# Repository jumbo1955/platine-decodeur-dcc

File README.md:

platine-decodeur-dcc

Schématiques et PCB pour décodeur DCC de locomotives N

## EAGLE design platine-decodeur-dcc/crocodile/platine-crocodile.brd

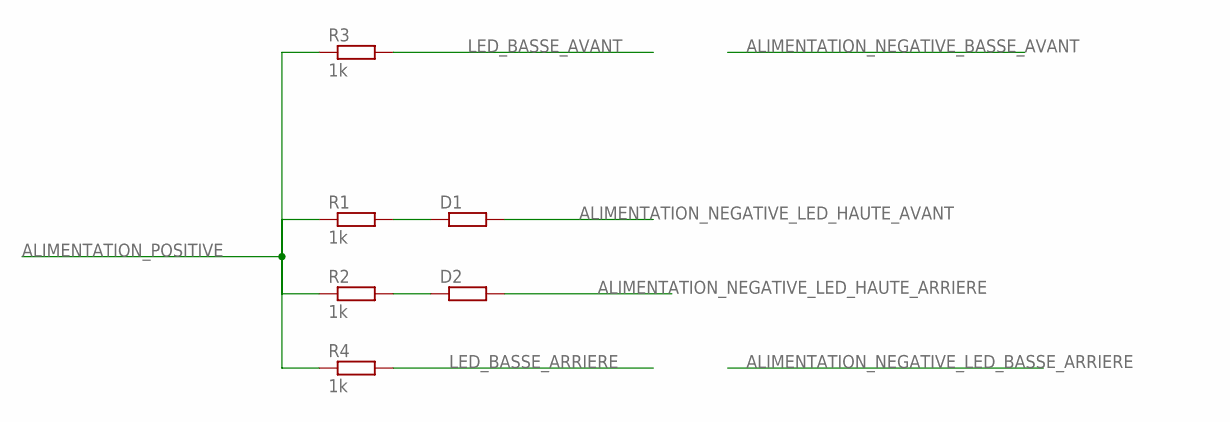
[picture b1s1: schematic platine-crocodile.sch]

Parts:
D1, D2: R-EU_M0805; M0805
R1, R2, R3, R4: 1k; M1206

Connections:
ALIMENTATION_NEGATIVE_LED_HAUTE_ARRIERE: D2.2
ALIMENTATION_NEGATIVE_LED_HAUTE_AVANT: D1.2
ALIMENTATION_POSITIVE: R1.1, R2.1, R3.1, R4.1
LED_BASSE_ARRIERE: R4.2
LED_BASSE_AVANT: R3.2
unnamed: D1.1, R1.2
unnamed: D2.1, R2.2

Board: 2 copper layers, 6 parts (0 on the bottom side), 3 nets, no tracks yet.

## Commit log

2022-10-15 init
2022-10-15 mise à jour readme
